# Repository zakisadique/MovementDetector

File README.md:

# MovementDetector
SDHD 24 GHz Movement Detector

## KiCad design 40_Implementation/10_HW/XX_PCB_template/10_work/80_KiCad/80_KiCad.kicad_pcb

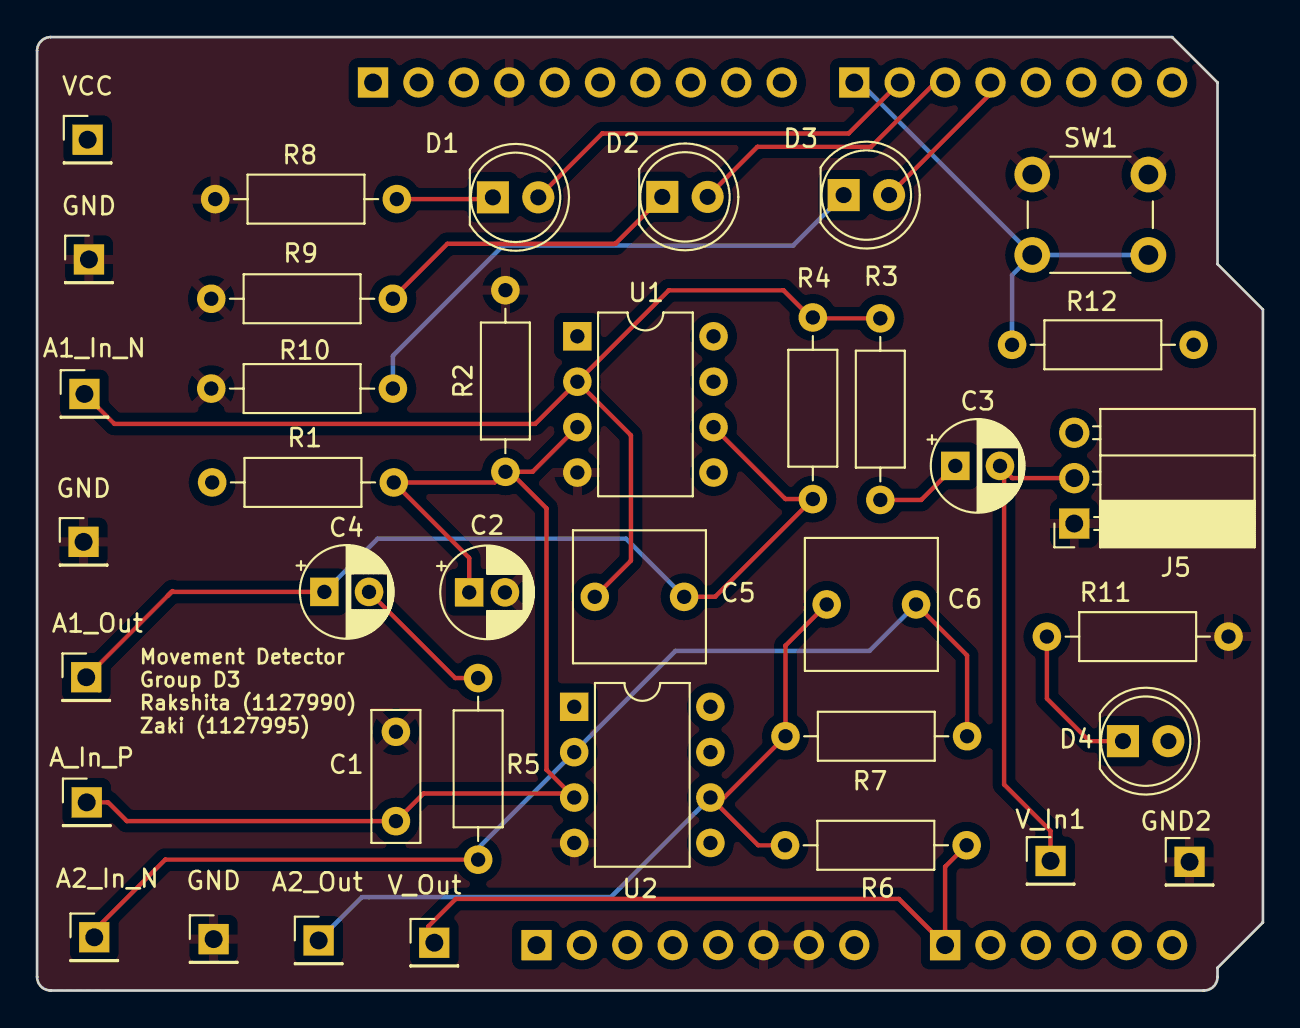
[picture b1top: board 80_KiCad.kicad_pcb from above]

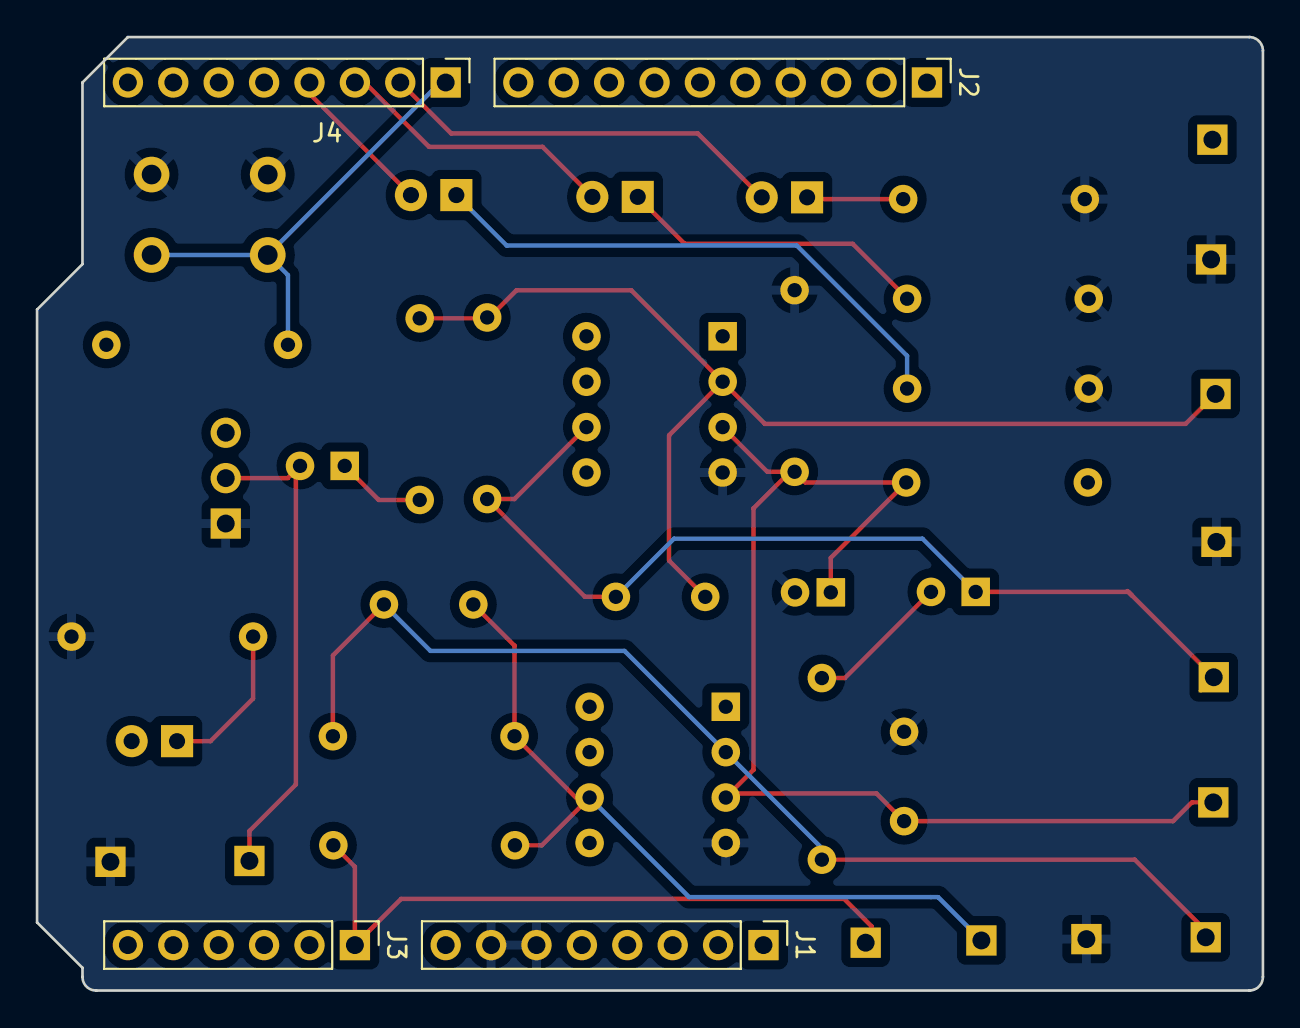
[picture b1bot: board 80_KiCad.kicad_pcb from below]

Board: 4 copper layers, 68.6 x 53.3 mm, 42 parts (4 on the bottom side), 19 nets.

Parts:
A1_In_N: TP_A1_In_N; PinHeader_1x01_P2.54mm_Vertical
A1_Out: TP_Vout1; PinHeader_1x01_P2.54mm_Vertical
A2_In_N: TP_A2_In_N; PinHeader_1x01_P2.54mm_Vertical
A2_Out: TP_Vout2; PinHeader_1x01_P2.54mm_Vertical
A_In_P: TP_A_in_P; PinHeader_1x01_P2.54mm_Vertical
C1: 100n; C_Rect_L7.2mm_W2.5mm_P5.00mm_FKS2_FKP2_MKS2_MKP2
C2: 22u; CP_Radial_D5.0mm_P2.00mm
C3, C4: 4.7u; CP_Radial_D5.0mm_P2.50mm
C5: 1.5n; C_Rect_L7.2mm_W7.2mm_P5.00mm_FKS2_FKP2_MKS2_MKP2
C6: 3.3n; C_Rect_L7.2mm_W7.2mm_P5.00mm_FKS2_FKP2_MKS2_MKP2
D1: LED Red; LED_D5.0mm
D2: LED Orange; LED_D5.0mm
D3: LED Green; LED_D5.0mm
D4: Power LED; LED_D5.0mm
GND, GND2: TP_GND; PinHeader_1x01_P2.54mm_Vertical
GND#2: TP_GND; PinHeader_1x01_P2.54mm_Vertical
GND#3: GND; PinHeader_1x01_P2.54mm_Vertical
J1: Power; PinHeader_1x08_P2.54mm_Vertical
J2: Digital/PWM; PinHeader_1x10_P2.54mm_Vertical
J3: Analog; PinHeader_1x06_P2.54mm_Vertical
J4: Digital/PWM; PinHeader_1x08_P2.54mm_Vertical
J5: Conn_01x03_Socket; PinSocket_1x03_P2.54mm_Horizontal
R1, R2: 1k; R_Axial_DIN0207_L6.3mm_D2.5mm_P10.16mm_Horizontal
R3: 2.2k; R_Axial_DIN0207_L6.3mm_D2.5mm_P10.16mm_Horizontal
R4: 220k; R_Axial_DIN0207_L6.3mm_D2.5mm_P10.16mm_Horizontal
R5: 33.3k; R_Axial_DIN0207_L6.3mm_D2.5mm_P10.16mm_Horizontal
R6: 100; R_Axial_DIN0207_L6.3mm_D2.5mm_P10.16mm_Horizontal
R7: 100k; R_Axial_DIN0207_L6.3mm_D2.5mm_P10.16mm_Horizontal
R8, R9, R10, R11: 330; R_Axial_DIN0207_L6.3mm_D2.5mm_P10.16mm_Horizontal
R12: 10k; R_Axial_DIN0207_L6.3mm_D2.5mm_P10.16mm_Horizontal
SW1: SW_SPST; SW_PUSH_6mm_H7.3mm
U1, U2: OPA340P; DIP-8_W7.62mm
VCC: VCC; PinHeader_1x01_P2.54mm_Vertical
V_In1: TP_Vin; PinHeader_1x01_P2.54mm_Vertical
V_Out: TP_Vout; PinHeader_1x01_P2.54mm_Vertical

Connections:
GND: C1.2, C2.2, GND.1, GND2.1, GND#2.1, GND#3.1, J1.6, J1.7, J2.4, J5.1, R2.2, R8.2, R9.1, R10.1, R11.2, SW1.2 (B), U1.4 (V-), U2.4 (V-)
Green: D3.2 (A), J4.4
unnamed: A1_Out.1, C4.1, C5.2, R4.2, U1.6
unnamed: A2_Out.1, C6.2, R6.1, R7.2, U2.6
unnamed: C3.1, R3.1
unnamed: C4.2, R5.1
unnamed: D1.1 (K), R8.1
unnamed: D2.1 (K), R9.2
unnamed: D3.1 (K), R10.2
unnamed: D4.1 (K), R11.1
unnamed: A_In_P.1, C1.1, C2.1, R1.2, R2.1, U1.3 (+), U2.3 (+)
unnamed: A1_In_N.1, C5.1, R3.2, R4.1, U1.2 (-)
unnamed: A2_In_N.1, C6.1, R5.2, R7.1, U2.2 (-)
Orange: D2.2 (A), J4.3
Push Button: J4.1, R12.1, SW1.1 (A)
Red: D1.2 (A), J4.2
VCC: D4.2 (A), J1.5, J5.3, R1.1, R12.2, U1.7 (V+), U2.7 (V+), VCC.1
Vin: C3.2, J5.2, V_In1.1
Vout: J3.1, R6.2, V_Out.1

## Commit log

2024-05-18 Review Submission
2024-05-18 Deleted .DS_Store
2024-05-19 Updated .gitignore
2024-05-19 v1.1
2024-05-19 v1.1.1
2024-05-19 Changed References - Silk Layer
2024-05-19 Changed References - Silk Layer - Minor Changes
2024-05-21 Before changes_21.05
2024-05-21 After capacitor change - 21.05s
2024-05-23 22.05
2024-05-26 Almost Submitted
2024-05-28 shakeup-workinig
2024-05-29 After Review 29.05
2024-06-01 LED & Analog Pin Config
2024-06-03 Before FFT and Button Switch (Pull Up)
2024-06-05 after amplifier - square wave
2024-06-09 working - sine wave 3v
2024-06-11 before ADC_DAC Off between states
2024-06-12 Before lab4
2024-06-12 idle - skipped; for testing on breadboard
2024-06-12 Updated pin configs to match schematics; works as expected
2024-06-21 lab 4
2024-06-21 not working yet 6.22 01:48
2024-06-22 unfinished not working
2024-06-22 Added FFT functionality and said FFT Buffer transfer over UART on PSOC
2024-07-06 before cfar - 06.07
2024-07-06 cfar and fft on matlab
2024-07-07 added LED logic;blink all if movement detected
2024-07-07 before switching to main
2024-07-08 before moving to FFT PSOC
2024-07-08 fixed matlab scaling
2024-07-08 FFt on PSOC works, sent to MATLAB, OK
2024-07-08 CFAR in MATLAB; LED On Movement
2024-07-08 cfaronpsoc - with radar
2024-07-09 dma_problem_rest_ok_ig
2024-07-09 before refactor
2024-07-09 present
2024-07-09 before changing led logic
2024-07-09 attempt with led speed
2024-07-09 attempt with led speed #2
2024-07-09 after refactor
2024-07-09 ready for review
2024-07-10 after final review
